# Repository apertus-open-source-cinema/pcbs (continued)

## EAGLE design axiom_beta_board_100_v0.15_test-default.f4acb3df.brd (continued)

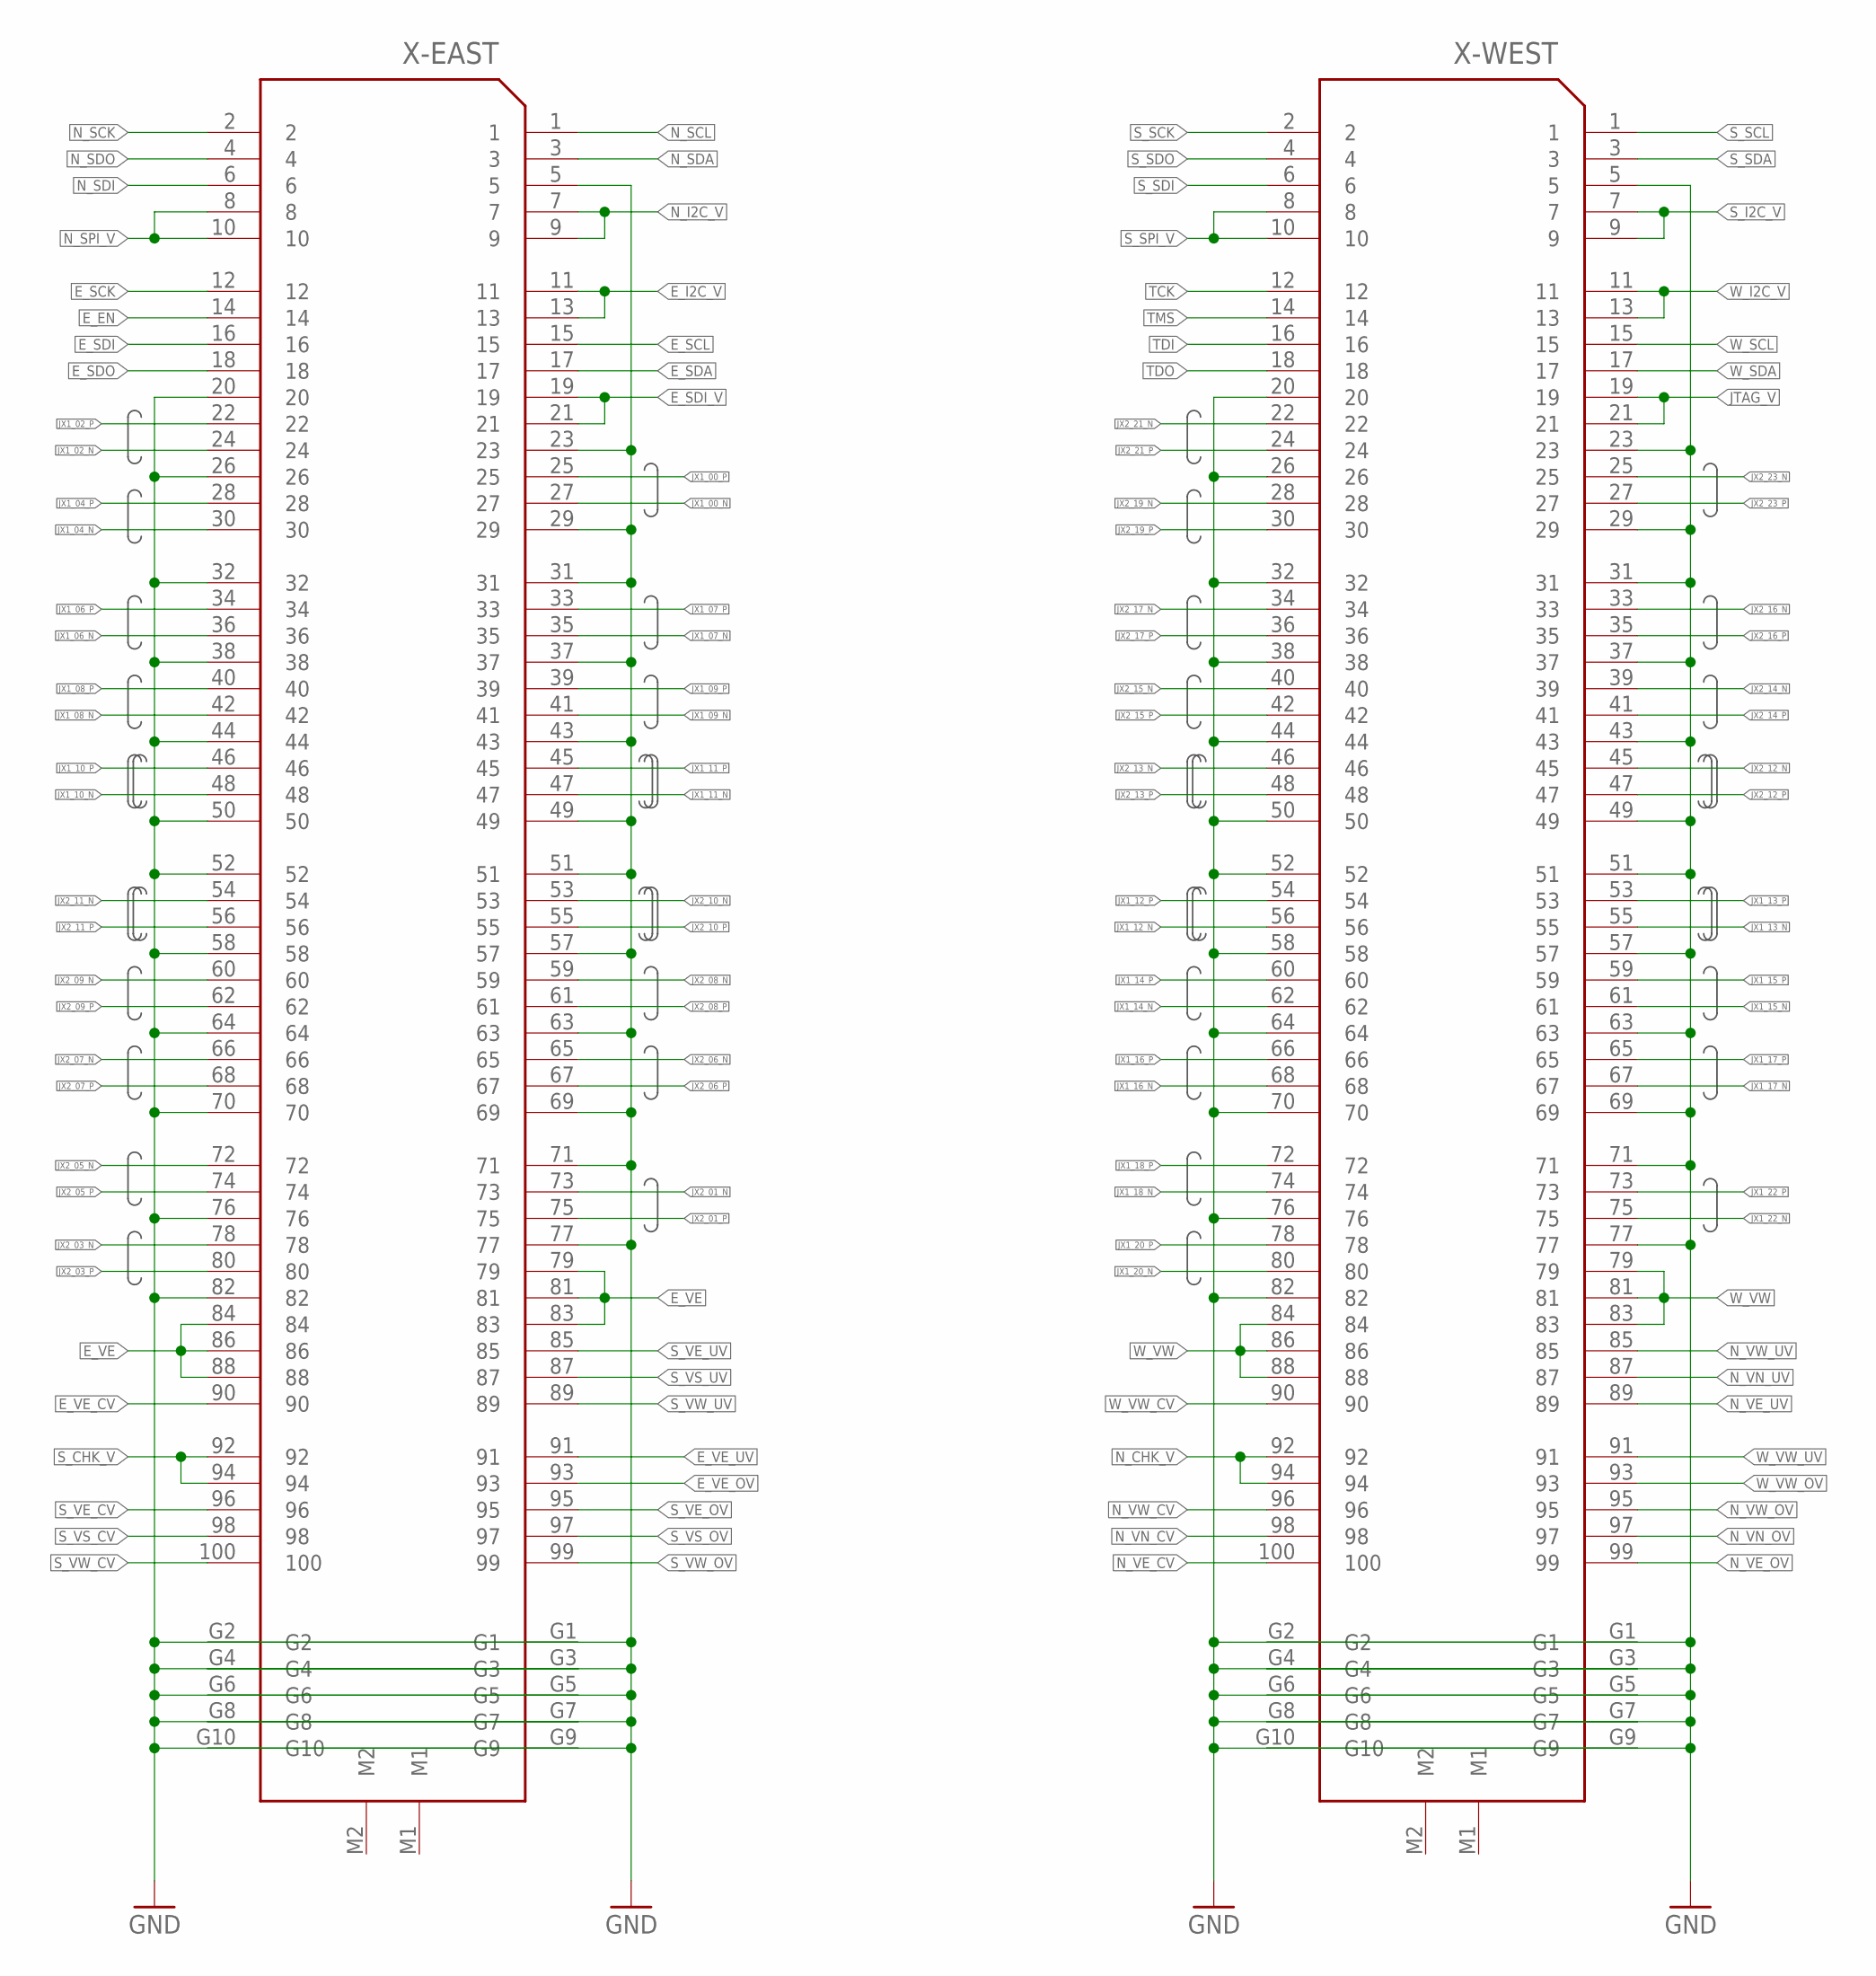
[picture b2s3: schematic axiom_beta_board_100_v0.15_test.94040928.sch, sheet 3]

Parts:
X-EAST: FX10-100/10S; FX10A-100S/10
X-WEST: FX10-100/10S; FX10A-100S/10

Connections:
E_EN: X-EAST.14; also elsewhere on the board
E_I2C_V: X-EAST.11, X-EAST.13; also elsewhere on the board
E_SCK: X-EAST.12; also elsewhere on the board
E_SCL: X-EAST.15; also elsewhere on the board
E_SDA: X-EAST.17; also elsewhere on the board
E_SDI: X-EAST.16; also elsewhere on the board
E_SDI_V: X-EAST.19, X-EAST.21; also elsewhere on the board
E_SDO: X-EAST.18; also elsewhere on the board
E_VE: X-EAST.79, X-EAST.81, X-EAST.83, X-EAST.84, X-EAST.86, X-EAST.88; also elsewhere on the board
E_VE_CV: X-EAST.90; also elsewhere on the board
E_VE_OV: X-EAST.93; also elsewhere on the board
E_VE_UV: X-EAST.91; also elsewhere on the board
GND: X-EAST.5, X-EAST.20, X-EAST.23, X-EAST.26, X-EAST.29, X-EAST.31, X-EAST.32, X-EAST.37, X-EAST.38, X-EAST.43, X-EAST.44, X-EAST.49, X-EAST.50, X-EAST.51, X-EAST.52, X-EAST.57, X-EAST.58, X-EAST.63, X-EAST.64, X-EAST.69, X-EAST.70, X-EAST.71, X-EAST.76, X-EAST.77, X-EAST.82, X-EAST.G1, X-EAST.G2, X-EAST.G3, X-EAST.G4, X-EAST.G5, X-EAST.G6, X-EAST.G7, X-EAST.G8, X-EAST.G9, X-EAST.G10, X-WEST.5, X-WEST.20, X-WEST.23, X-WEST.26, X-WEST.29, X-WEST.31, X-WEST.32, X-WEST.37, X-WEST.38, X-WEST.43, X-WEST.44, X-WEST.49, X-WEST.50, X-WEST.51, X-WEST.52, X-WEST.57, X-WEST.58, X-WEST.63, X-WEST.64, X-WEST.69, X-WEST.70, X-WEST.71, X-WEST.76, X-WEST.77, X-WEST.82, X-WEST.G1, X-WEST.G2, X-WEST.G3, X-WEST.G4, X-WEST.G5, X-WEST.G6, X-WEST.G7, X-WEST.G8, X-WEST.G9, X-WEST.G10; also elsewhere on the board
JTAG_V: X-WEST.19, X-WEST.21; also elsewhere on the board
JX1_00_N: X-EAST.27; also elsewhere on the board
JX1_00_P: X-EAST.25; also elsewhere on the board
JX1_02_N: X-EAST.24; also elsewhere on the board
JX1_02_P: X-EAST.22; also elsewhere on the board
JX1_04_N: X-EAST.30; also elsewhere on the board
JX1_04_P: X-EAST.28; also elsewhere on the board
JX1_06_N: X-EAST.36; also elsewhere on the board
JX1_06_P: X-EAST.34; also elsewhere on the board
JX1_07_N: X-EAST.35; also elsewhere on the board
JX1_07_P: X-EAST.33; also elsewhere on the board
JX1_08_N: X-EAST.42; also elsewhere on the board
JX1_08_P: X-EAST.40; also elsewhere on the board
JX1_09_N: X-EAST.41; also elsewhere on the board
JX1_09_P: X-EAST.39; also elsewhere on the board
JX1_10_N: X-EAST.48; also elsewhere on the board
JX1_10_P: X-EAST.46; also elsewhere on the board
JX1_11_N: X-EAST.47; also elsewhere on the board
JX1_11_P: X-EAST.45; also elsewhere on the board
JX1_12_N: X-WEST.56; also elsewhere on the board
JX1_12_P: X-WEST.54; also elsewhere on the board
JX1_13_N: X-WEST.55; also elsewhere on the board
JX1_13_P: X-WEST.53; also elsewhere on the board
JX1_14_N: X-WEST.62; also elsewhere on the board
JX1_14_P: X-WEST.60; also elsewhere on the board
JX1_15_N: X-WEST.61; also elsewhere on the board
JX1_15_P: X-WEST.59; also elsewhere on the board
JX1_16_N: X-WEST.68; also elsewhere on the board
JX1_16_P: X-WEST.66; also elsewhere on the board
JX1_17_N: X-WEST.67; also elsewhere on the board
JX1_17_P: X-WEST.65; also elsewhere on the board
JX1_18_N: X-WEST.74; also elsewhere on the board
JX1_18_P: X-WEST.72; also elsewhere on the board
JX1_20_N: X-WEST.80; also elsewhere on the board
JX1_20_P: X-WEST.78; also elsewhere on the board
JX1_22_N: X-WEST.75; also elsewhere on the board
JX1_22_P: X-WEST.73; also elsewhere on the board
JX2_01_N: X-EAST.73; also elsewhere on the board
JX2_01_P: X-EAST.75; also elsewhere on the board
JX2_03_N: X-EAST.78; also elsewhere on the board
JX2_03_P: X-EAST.80; also elsewhere on the board
JX2_05_N: X-EAST.72; also elsewhere on the board
JX2_05_P: X-EAST.74; also elsewhere on the board
JX2_06_N: X-EAST.65; also elsewhere on the board
JX2_06_P: X-EAST.67; also elsewhere on the board
JX2_07_N: X-EAST.66; also elsewhere on the board
JX2_07_P: X-EAST.68; also elsewhere on the board
JX2_08_N: X-EAST.59; also elsewhere on the board
JX2_08_P: X-EAST.61; also elsewhere on the board
JX2_09_N: X-EAST.60; also elsewhere on the board
JX2_09_P: X-EAST.62; also elsewhere on the board
JX2_10_N: X-EAST.53; also elsewhere on the board
JX2_10_P: X-EAST.55; also elsewhere on the board
JX2_11_N: X-EAST.54; also elsewhere on the board
JX2_11_P: X-EAST.56; also elsewhere on the board
JX2_12_N: X-WEST.45; also elsewhere on the board
JX2_12_P: X-WEST.47; also elsewhere on the board
JX2_13_N: X-WEST.46; also elsewhere on the board
JX2_13_P: X-WEST.48; also elsewhere on the board
JX2_14_N: X-WEST.39; also elsewhere on the board
JX2_14_P: X-WEST.41; also elsewhere on the board
JX2_15_N: X-WEST.40; also elsewhere on the board
JX2_15_P: X-WEST.42; also elsewhere on the board
JX2_16_N: X-WEST.33; also elsewhere on the board
JX2_16_P: X-WEST.35; also elsewhere on the board
JX2_17_N: X-WEST.34; also elsewhere on the board
JX2_17_P: X-WEST.36; also elsewhere on the board
JX2_19_N: X-WEST.28; also elsewhere on the board
JX2_19_P: X-WEST.30; also elsewhere on the board
JX2_21_N: X-WEST.22; also elsewhere on the board
JX2_21_P: X-WEST.24; also elsewhere on the board
JX2_23_N: X-WEST.25; also elsewhere on the board
JX2_23_P: X-WEST.27; also elsewhere on the board
N_CHK_V: X-WEST.92, X-WEST.94; also elsewhere on the board
N_I2C_V: X-EAST.7, X-EAST.9; also elsewhere on the board
N_SCK: X-EAST.2; also elsewhere on the board
N_SCL: X-EAST.1; also elsewhere on the board
N_SDA: X-EAST.3; also elsewhere on the board
N_SDI: X-EAST.6; also elsewhere on the board
N_SDO: X-EAST.4; also elsewhere on the board
N_SPI_V: X-EAST.8, X-EAST.10; also elsewhere on the board
N_VE_CV: X-WEST.100; also elsewhere on the board
N_VE_OV: X-WEST.99; also elsewhere on the board
N_VE_UV: X-WEST.89; also elsewhere on the board
N_VN_CV: X-WEST.98; also elsewhere on the board
N_VN_OV: X-WEST.97; also elsewhere on the board
N_VN_UV: X-WEST.87; also elsewhere on the board
N_VW_CV: X-WEST.96; also elsewhere on the board
N_VW_OV: X-WEST.95; also elsewhere on the board
N_VW_UV: X-WEST.85; also elsewhere on the board
S_CHK_V: X-EAST.92, X-EAST.94; also elsewhere on the board
S_I2C_V: X-WEST.7, X-WEST.9; also elsewhere on the board
S_SCK: X-WEST.2; also elsewhere on the board
S_SCL: X-WEST.1; also elsewhere on the board
S_SDA: X-WEST.3; also elsewhere on the board
S_SDI: X-WEST.6; also elsewhere on the board
S_SDO: X-WEST.4; also elsewhere on the board
S_SPI_V: X-WEST.8, X-WEST.10; also elsewhere on the board
S_VE_CV: X-EAST.96; also elsewhere on the board
S_VE_OV: X-EAST.95; also elsewhere on the board
S_VE_UV: X-EAST.85; also elsewhere on the board
S_VS_CV: X-EAST.98; also elsewhere on the board
S_VS_OV: X-EAST.97; also elsewhere on the board
S_VS_UV: X-EAST.87; also elsewhere on the board
S_VW_CV: X-EAST.100; also elsewhere on the board
S_VW_OV: X-EAST.99; also elsewhere on the board
S_VW_UV: X-EAST.89; also elsewhere on the board
TCK: X-WEST.12; also elsewhere on the board
TDI: X-WEST.16; also elsewhere on the board
TDO: X-WEST.18; also elsewhere on the board
TMS: X-WEST.14; also elsewhere on the board
W_I2C_V: X-WEST.11, X-WEST.13; also elsewhere on the board
W_SCL: X-WEST.15; also elsewhere on the board
W_SDA: X-WEST.17; also elsewhere on the board
W_VW: X-WEST.79, X-WEST.81, X-WEST.83, X-WEST.84, X-WEST.86, X-WEST.88; also elsewhere on the board
W_VW_CV: X-WEST.90; also elsewhere on the board
W_VW_OV: X-WEST.93; also elsewhere on the board
W_VW_UV: X-WEST.91; also elsewhere on the board

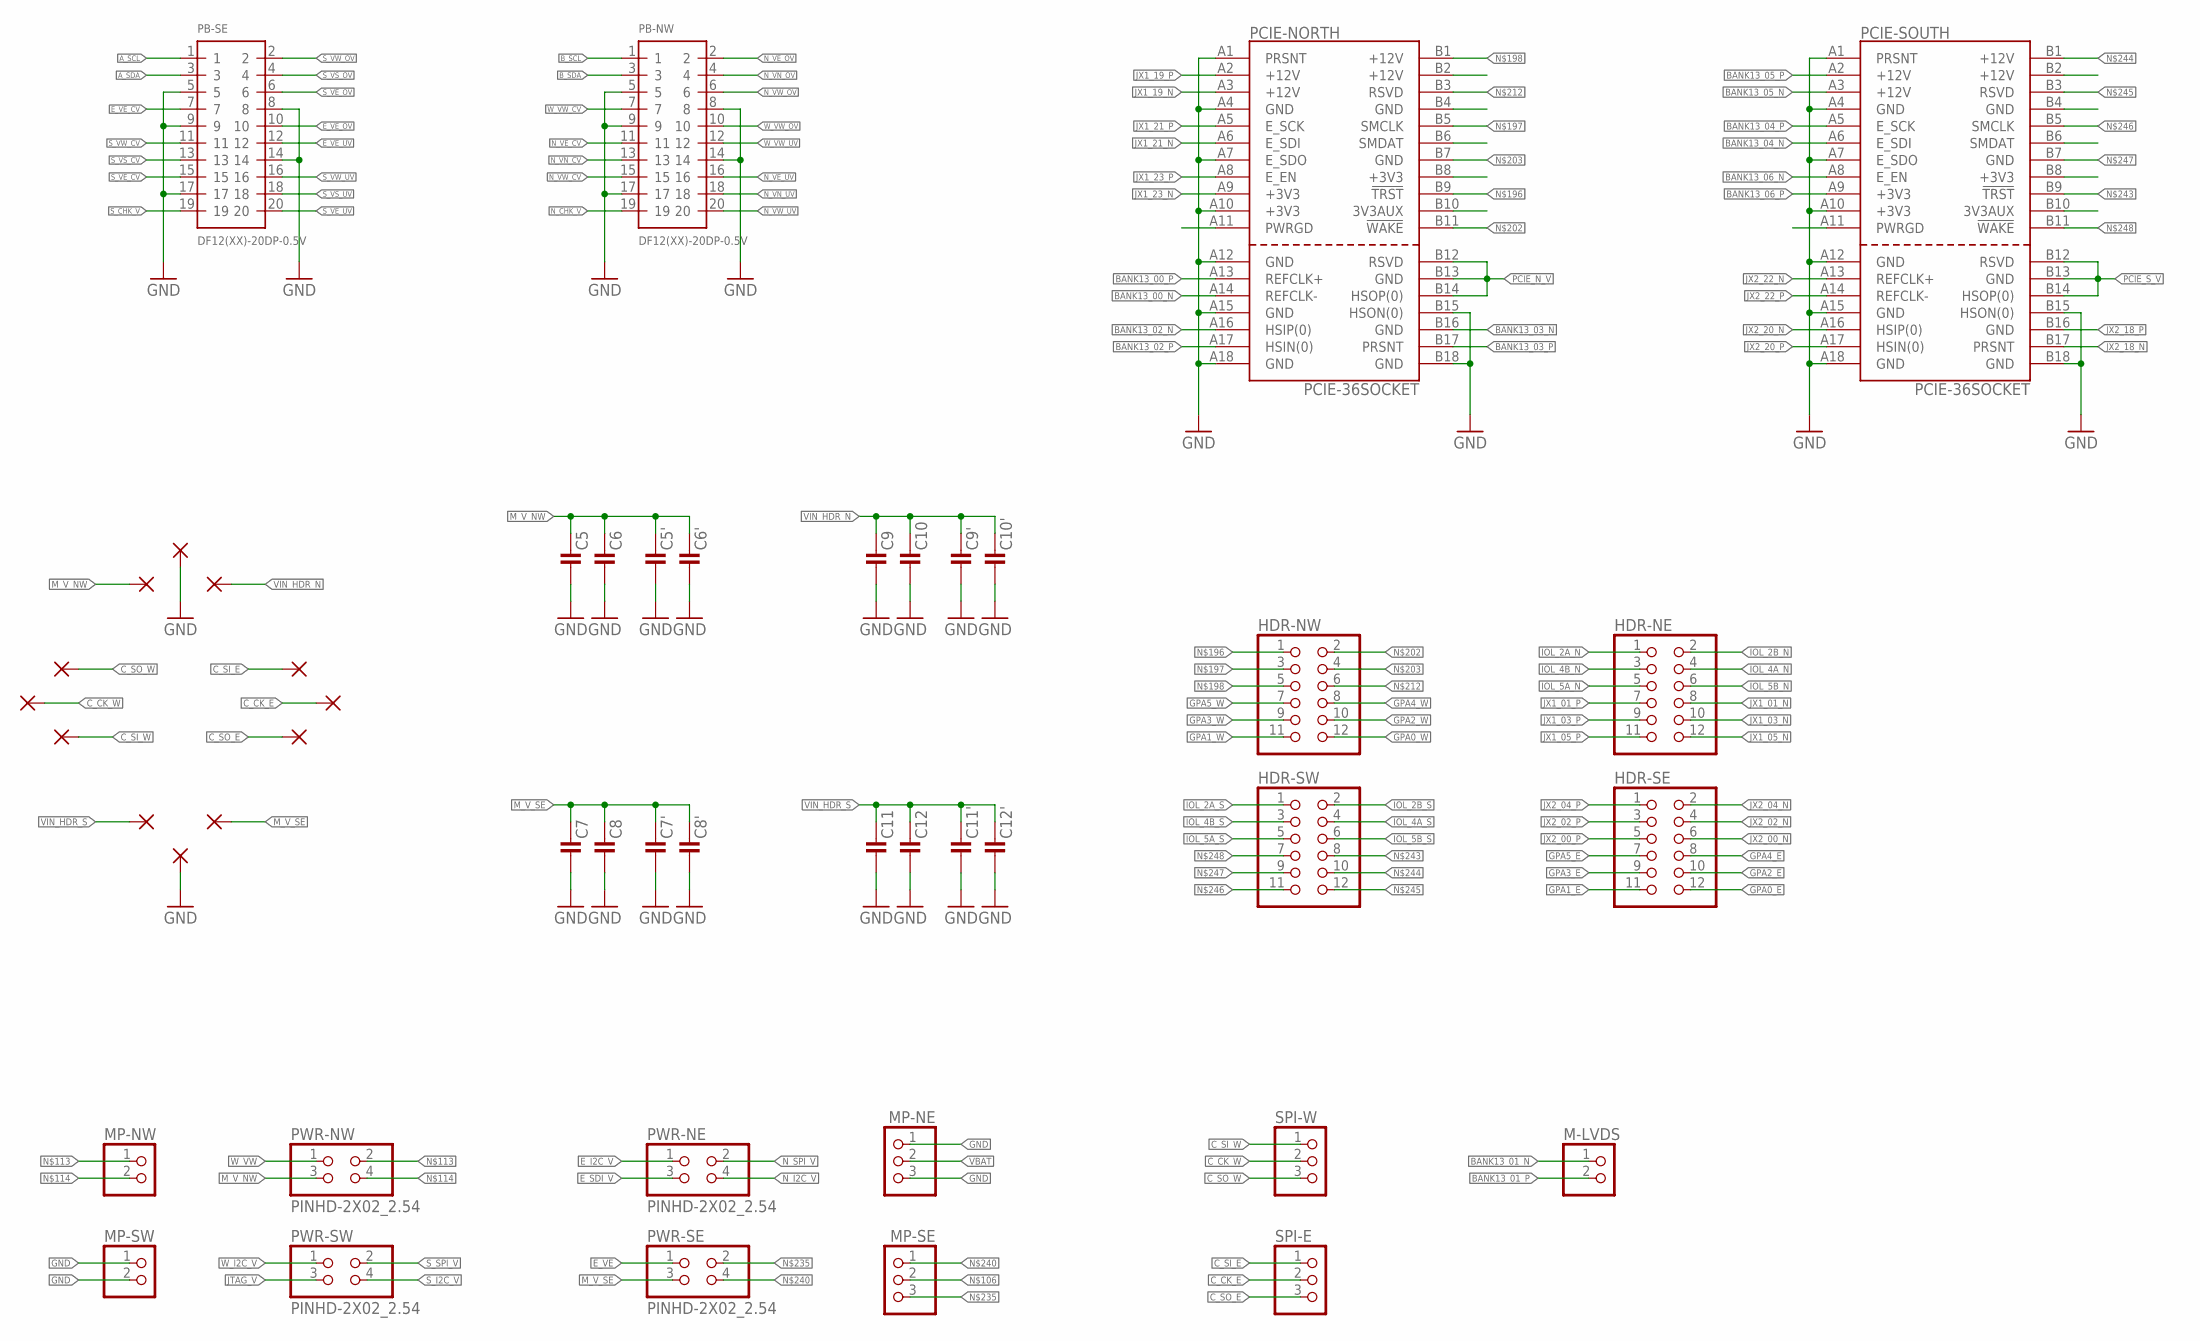
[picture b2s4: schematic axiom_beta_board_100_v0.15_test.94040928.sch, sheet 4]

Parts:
C5, C5', C7, C7', C9, C9', C11, C11': C0805-A; 0805-A
C6, C6', C8, C8', C10, C10', C12, C12': C0603-A; 0603-A
HDR-NE: PINHD-2X06_2.00; 2X06M
HDR-NW: PINHD-2X06_2.00; 2X06M
HDR-SE: PINHD-2X06_2.00; 2X06M
HDR-SW: PINHD-2X06_2.00; 2X06M
M-LVDS: PINHD-1X02_2.00; 1X02M
MP-NE: PINHD-1X03_2.00; 1X03M
MP-NW: PINHD-1X02_2.00; 1X02M
MP-SE: PINHD-1X03_2.00; 1X03M
MP-SW: PINHD-1X02_2.00; 1X02M
PB-NW: DF12(XX)-20DP-0.5V
PB-SE: DF12(XX)-20DP-0.5V
PCIE-NORTH: PCIE-36SOCKET; PCIE-36
PCIE-SOUTH: PCIE-36SOCKET; PCIE-36
PWR-NE: PINHD-2X02_2.54; 2X02
PWR-NW: PINHD-2X02_2.54; 2X02
PWR-SE: PINHD-2X02_2.54; 2X02
PWR-SW: PINHD-2X02_2.54; 2X02
SPI-E: PINHD-2X02_2.00; 1X03M
SPI-W: PINHD-2X02_2.00; 1X03M
U$1, U$2, U$11, U$14, U$15, U$16, U$17, U$18, U$19, U$20, U$21, U$22: PINPAD1.27MM; 1.2/0.6

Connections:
BANK13_00_N: PCIE-NORTH.A14 (LVDS_3B); also elsewhere on the board
BANK13_00_P: PCIE-NORTH.A13 (LVDS_3A); also elsewhere on the board
BANK13_01_N: M-LVDS.1; also elsewhere on the board
BANK13_01_P: M-LVDS.2; also elsewhere on the board
BANK13_02_N: PCIE-NORTH.A16 (LVDS_4A); also elsewhere on the board
BANK13_02_P: PCIE-NORTH.A17 (LVDS_4B); also elsewhere on the board
BANK13_03_N: PCIE-NORTH.B16 (LVDS_5A); also elsewhere on the board
BANK13_03_P: PCIE-NORTH.B17 (LVDS_5B); also elsewhere on the board
BANK13_04_N: PCIE-SOUTH.A6 (LVDS_1B); also elsewhere on the board
BANK13_04_P: PCIE-SOUTH.A5 (LVDS_1A); also elsewhere on the board
BANK13_05_N: PCIE-SOUTH.A3 (LVDS_0B); also elsewhere on the board
BANK13_05_P: PCIE-SOUTH.A2 (LVDS_0A); also elsewhere on the board
BANK13_06_N: PCIE-SOUTH.A8 (LVDS_2A); also elsewhere on the board
BANK13_06_P: PCIE-SOUTH.A9 (LVDS_2B); also elsewhere on the board
C_CK_E: SPI-E.2, U$14.1
C_CK_W: SPI-W.2, U$1.1
C_SI_E: SPI-E.1, U$15.1
C_SI_W: SPI-W.1, U$2.1
C_SO_E: SPI-E.3, U$16.1
C_SO_W: SPI-W.3, U$11.1
E_I2C_V: PWR-NE.1; also elsewhere on the board
E_SDI_V: PWR-NE.3; also elsewhere on the board
E_VE: PWR-SE.1; also elsewhere on the board
E_VE_CV: PB-SE.7; also elsewhere on the board
E_VE_OV: PB-SE.10; also elsewhere on the board
E_VE_UV: PB-SE.12; also elsewhere on the board
GND: C5.2, C5'.2, C6.2, C6'.2, C7.2, C7'.2, C8.2, C8'.2, C9.2, C9'.2, C10.2, C10'.2, C11.2, C11'.2, C12.2, C12'.2, MP-NE.1, MP-NE.3, MP-SW.1, MP-SW.2, PB-NW.5, PB-NW.8, PB-NW.9, PB-NW.14, PB-NW.17, PB-SE.5, PB-SE.8, PB-SE.9, PB-SE.14, PB-SE.17, PCIE-NORTH.A1 (GND), PCIE-NORTH.A4 (GND), PCIE-NORTH.A7 (GND), PCIE-NORTH.A10 (GND), PCIE-NORTH.A12 (GND), PCIE-NORTH.A15 (GND), PCIE-NORTH.A18 (GND), PCIE-NORTH.B15 (GND), PCIE-NORTH.B18 (GND), PCIE-SOUTH.A1 (GND), PCIE-SOUTH.A4 (GND), PCIE-SOUTH.A7 (GND), PCIE-SOUTH.A10 (GND), PCIE-SOUTH.A12 (GND), PCIE-SOUTH.A15 (GND), PCIE-SOUTH.A18 (GND), PCIE-SOUTH.B15 (GND), PCIE-SOUTH.B18 (GND), U$17.1, U$20.1; also elsewhere on the board
GPA0_E: HDR-SE.12; also elsewhere on the board
GPA0_W: HDR-NW.12; also elsewhere on the board
GPA1_E: HDR-SE.11; also elsewhere on the board
GPA1_W: HDR-NW.11; also elsewhere on the board
GPA2_E: HDR-SE.10; also elsewhere on the board
GPA2_W: HDR-NW.10; also elsewhere on the board
GPA3_E: HDR-SE.9; also elsewhere on the board
GPA3_W: HDR-NW.9; also elsewhere on the board
GPA4_E: HDR-SE.8; also elsewhere on the board
GPA4_W: HDR-NW.8; also elsewhere on the board
GPA5_E: HDR-SE.7; also elsewhere on the board
GPA5_W: HDR-NW.7; also elsewhere on the board
IOL_2A_N: HDR-NE.1; also elsewhere on the board
IOL_2A_S: HDR-SW.1; also elsewhere on the board
IOL_2B_N: HDR-NE.2; also elsewhere on the board
IOL_2B_S: HDR-SW.2; also elsewhere on the board
IOL_4A_N: HDR-NE.4; also elsewhere on the board
IOL_4A_S: HDR-SW.4; also elsewhere on the board
IOL_4B_N: HDR-NE.3; also elsewhere on the board
IOL_4B_S: HDR-SW.3; also elsewhere on the board
IOL_5A_N: HDR-NE.5; also elsewhere on the board
IOL_5A_S: HDR-SW.5; also elsewhere on the board
IOL_5B_N: HDR-NE.6; also elsewhere on the board
IOL_5B_S: HDR-SW.6; also elsewhere on the board
JTAG_V: PWR-SW.3; also elsewhere on the board
JX1_01_N: HDR-NE.8; also elsewhere on the board
JX1_01_P: HDR-NE.7; also elsewhere on the board
JX1_03_N: HDR-NE.10; also elsewhere on the board
JX1_03_P: HDR-NE.9; also elsewhere on the board
JX1_05_N: HDR-NE.12; also elsewhere on the board
JX1_05_P: HDR-NE.11; also elsewhere on the board
JX1_19_N: PCIE-NORTH.A3 (LVDS_0B); also elsewhere on the board
JX1_19_P: PCIE-NORTH.A2 (LVDS_0A); also elsewhere on the board
JX1_21_N: PCIE-NORTH.A6 (LVDS_1B); also elsewhere on the board
JX1_21_P: PCIE-NORTH.A5 (LVDS_1A); also elsewhere on the board
JX1_23_N: PCIE-NORTH.A9 (LVDS_2B); also elsewhere on the board
JX1_23_P: PCIE-NORTH.A8 (LVDS_2A); also elsewhere on the board
JX2_00_N: HDR-SE.6; also elsewhere on the board
JX2_00_P: HDR-SE.5; also elsewhere on the board
JX2_02_N: HDR-SE.4; also elsewhere on the board
JX2_02_P: HDR-SE.3; also elsewhere on the board
JX2_04_N: HDR-SE.2; also elsewhere on the board
JX2_04_P: HDR-SE.1; also elsewhere on the board
JX2_18_N: PCIE-SOUTH.B17 (LVDS_5B); also elsewhere on the board
JX2_18_P: PCIE-SOUTH.B16 (LVDS_5A); also elsewhere on the board
JX2_20_N: PCIE-SOUTH.A16 (LVDS_4A); also elsewhere on the board
JX2_20_P: PCIE-SOUTH.A17 (LVDS_4B); also elsewhere on the board
JX2_22_N: PCIE-SOUTH.A13 (LVDS_3A); also elsewhere on the board
JX2_22_P: PCIE-SOUTH.A14 (LVDS_3B); also elsewhere on the board
M_V_NW: C5.1, C5'.1, C6.1, C6'.1, PWR-NW.3, U$18.1; also elsewhere on the board
M_V_SE: C7.1, C7'.1, C8.1, C8'.1, PWR-SE.3, U$21.1; also elsewhere on the board
unnamed 266: MP-SE.2; also elsewhere on the board
unnamed: MP-NW.1, PWR-NW.2
unnamed: MP-NW.2, PWR-NW.4
unnamed: HDR-NW.1, PCIE-NORTH.B9 (IO8)
unnamed: HDR-NW.3, PCIE-NORTH.B5 (IO4)
unnamed: HDR-NW.5, PCIE-NORTH.B1 (IO0)
unnamed: HDR-NW.2, PCIE-NORTH.B11 (IO10)
unnamed: HDR-NW.4, PCIE-NORTH.B7 (IO6)
unnamed: HDR-NW.6, PCIE-NORTH.B3 (IO2)
unnamed: MP-SE.3, PWR-SE.2
unnamed: MP-SE.1, PWR-SE.4
unnamed: HDR-SW.8, PCIE-SOUTH.B9 (IO8)
unnamed: HDR-SW.10, PCIE-SOUTH.B1 (IO0)
unnamed: HDR-SW.12, PCIE-SOUTH.B3 (IO2)
unnamed: HDR-SW.11, PCIE-SOUTH.B5 (IO4)
unnamed: HDR-SW.9, PCIE-SOUTH.B7 (IO6)
unnamed: HDR-SW.7, PCIE-SOUTH.B11 (IO10)
N_CHK_V: PB-NW.19; also elsewhere on the board
N_I2C_V: PWR-NE.4; also elsewhere on the board
N_SPI_V: PWR-NE.2; also elsewhere on the board
N_VE_CV: PB-NW.11; also elsewhere on the board
N_VE_OV: PB-NW.2; also elsewhere on the board
N_VE_UV: PB-NW.16; also elsewhere on the board
N_VN_CV: PB-NW.13; also elsewhere on the board
N_VN_OV: PB-NW.4; also elsewhere on the board
N_VN_UV: PB-NW.18; also elsewhere on the board
N_VW_CV: PB-NW.15; also elsewhere on the board
N_VW_OV: PB-NW.6; also elsewhere on the board
N_VW_UV: PB-NW.20; also elsewhere on the board
PCIE_N_V: PCIE-NORTH.B12 (VCC), PCIE-NORTH.B13 (VCC), PCIE-NORTH.B14 (VCC); also elsewhere on the board
PCIE_S_V: PCIE-SOUTH.B12 (VCC), PCIE-SOUTH.B13 (VCC), PCIE-SOUTH.B14 (VCC); also elsewhere on the board
S_CHK_V: PB-SE.19; also elsewhere on the board
S_I2C_V: PWR-SW.4; also elsewhere on the board
S_SPI_V: PWR-SW.2; also elsewhere on the board
S_VE_CV: PB-SE.15; also elsewhere on the board
S_VE_OV: PB-SE.6; also elsewhere on the board
S_VE_UV: PB-SE.20; also elsewhere on the board
S_VS_CV: PB-SE.13; also elsewhere on the board
S_VS_OV: PB-SE.4; also elsewhere on the board
S_VS_UV: PB-SE.18; also elsewhere on the board
S_VW_CV: PB-SE.11; also elsewhere on the board
S_VW_OV: PB-SE.2; also elsewhere on the board
S_VW_UV: PB-SE.16; also elsewhere on the board
VBAT: MP-NE.2; also elsewhere on the board
VIN_HDR_N: C9.1, C9'.1, C10.1, C10'.1, U$19.1; also elsewhere on the board
VIN_HDR_S: C11.1, C11'.1, C12.1, C12'.1, U$22.1; also elsewhere on the board
W_I2C_V: PWR-SW.1; also elsewhere on the board
W_VW: PWR-NW.1; also elsewhere on the board
W_VW_CV: PB-NW.7; also elsewhere on the board
W_VW_OV: PB-NW.10; also elsewhere on the board
W_VW_UV: PB-NW.12; also elsewhere on the board
